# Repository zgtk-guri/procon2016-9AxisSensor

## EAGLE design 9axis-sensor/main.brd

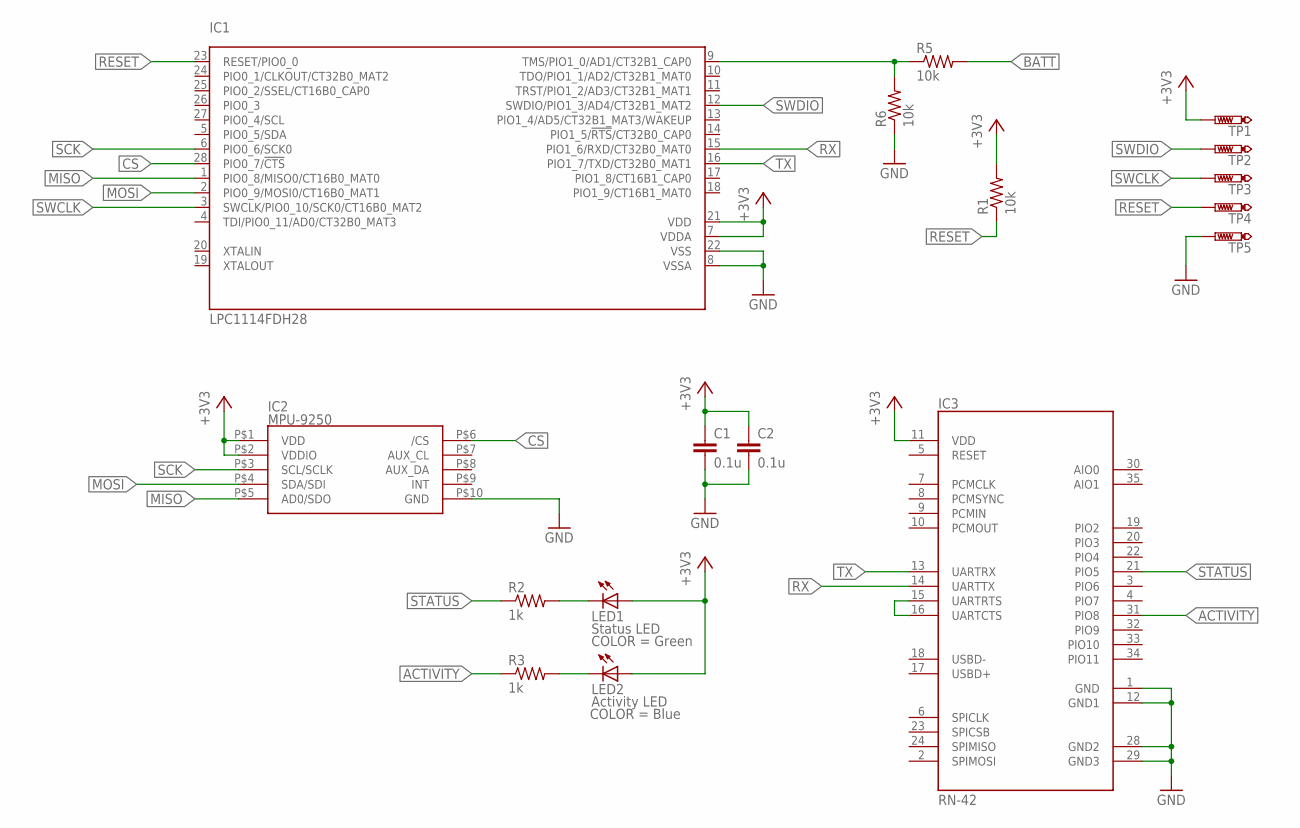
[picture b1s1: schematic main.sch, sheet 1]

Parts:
C1, C2: 0.1u; C0603
IC1: LPC1114FDH28; SOT361-1; MPN LPC1114FDH28/102
IC2: MPU-9250; DIP10S
IC3: RN-42; RN41; MPN RN-42-I/RM
LED1: Status LED; CHIP-LED0603; MPN OSYG1608C1A
LED2: Activity LED; CHIP-LED0603; MPN OSBL1608C1A
R1, R5, R6: 10k; R0603
R2, R3: 1k; R0603
TP1: 3V3; B1,27
TP2: SWDIO; B1,27
TP3: SWCLK; B1,27
TP4: RESET; B1,27
TP5: GND; B1,27

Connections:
+3V3: C1.1, C2.1, IC1.7 (VDDA), IC1.21 (VDD), IC2.P$1 (VDD), IC2.P$2 (VDDIO), IC3.11 (VDD), LED1.A, LED2.A, R1.2, TP1.TP; also elsewhere on the board
ACTIVITY: IC3.31 (PIO8), R3.1
BATT: R5.2; also elsewhere on the board
CS: IC1.28 (PIO0_7/!CTS!), IC2.P$6 (/CS)
GND: C1.2, C2.2, IC1.8 (VSSA), IC1.22 (VSS), IC2.P$10 (GND), IC3.1 (GND), IC3.12 (GND1), IC3.28 (GND2), IC3.29 (GND3), R6.1, TP5.TP; also elsewhere on the board
MISO: IC1.1 (PIO0_8/MISO0/CT16B0_MAT0), IC2.P$5 (AD0/SDO)
MOSI: IC1.2 (PIO0_9/MOSI0/CT16B0_MAT1), IC2.P$4 (SDA/SDI)
unnamed: IC3.15 (UARTRTS), IC3.16 (UARTCTS)
unnamed: LED1.C, R2.2
unnamed: LED2.C, R3.2
unnamed: IC1.9 (TMS/PIO1_0/AD1/CT32B1_CAP0), R5.1, R6.2
RESET: IC1.23 (RESET/PIO0_0), R1.1, TP4.TP
RX: IC1.15 (PIO1_6/RXD/CT32B0_MAT0), IC3.14 (UARTTX)
SCK: IC1.6 (PIO0_6/SCK0), IC2.P$3 (SCL/SCLK)
STATUS: IC3.21 (PIO5), R2.1
SWCLK: IC1.3 (SWCLK/PIO0_10/SCK0/CT16B0_MAT2), TP3.TP
SWDIO: IC1.12 (SWDIO/PIO1_3/AD4/CT32B1_MAT2), TP2.TP
TX: IC1.16 (PIO1_7/TXD/CT32B0_MAT1), IC3.13 (UARTRX)

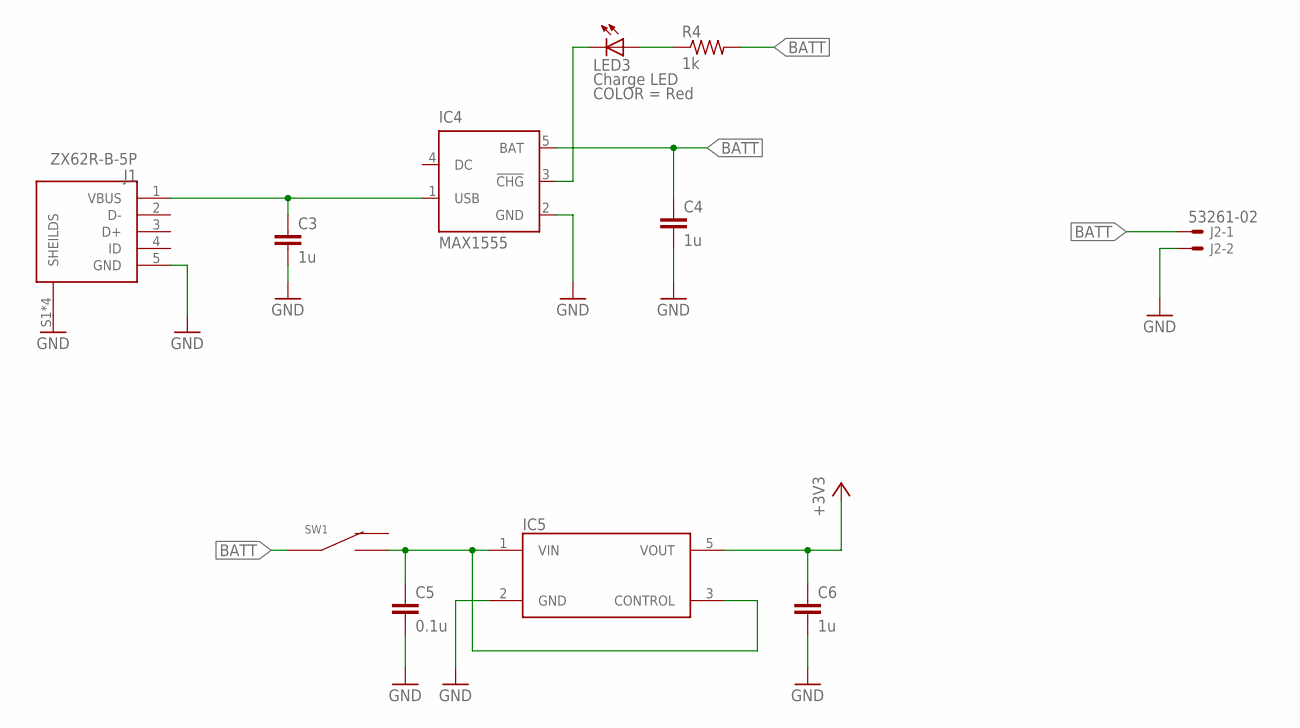
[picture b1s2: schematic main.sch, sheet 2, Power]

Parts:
C3, C4, C6: 1u; C0603
C5: 0.1u; C0603
IC4: MAX1555; SOT23-5L
IC5: NJM2866F33; SOT23-5L
J1: ZX62R-B-5P; MPN ZX62R-B-5P
J2: 53261-02; MPN 53261-0271
LED3: Charge LED; CHIP-LED0603; MPN OSHR1608C1A
R4: 1k; R0603
SW1: SK-12D01-VG4

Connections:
+3V3: C6.1, IC5.5 (VOUT); also elsewhere on the board
BATT: C4.1, IC4.5 (BAT), J2.1, R4.2, SW1.P$2; also elsewhere on the board
GND: C3.2, C4.2, C5.2, C6.2, IC4.2 (GND), IC5.2 (GND), J1.5 (GND), J1.S1 (SHEILDS), J1.S2 (SHEILDS), J1.S3 (SHEILDS), J1.S4 (SHEILDS), J2.2; also elsewhere on the board
unnamed: C3.1, IC4.1 (USB), J1.1 (VBUS)
unnamed: IC4.3 (!CHG), LED3.C
unnamed: LED3.A, R4.1
unnamed: C5.1, IC5.1 (VIN), IC5.3 (CONTROL), SW1.P$3

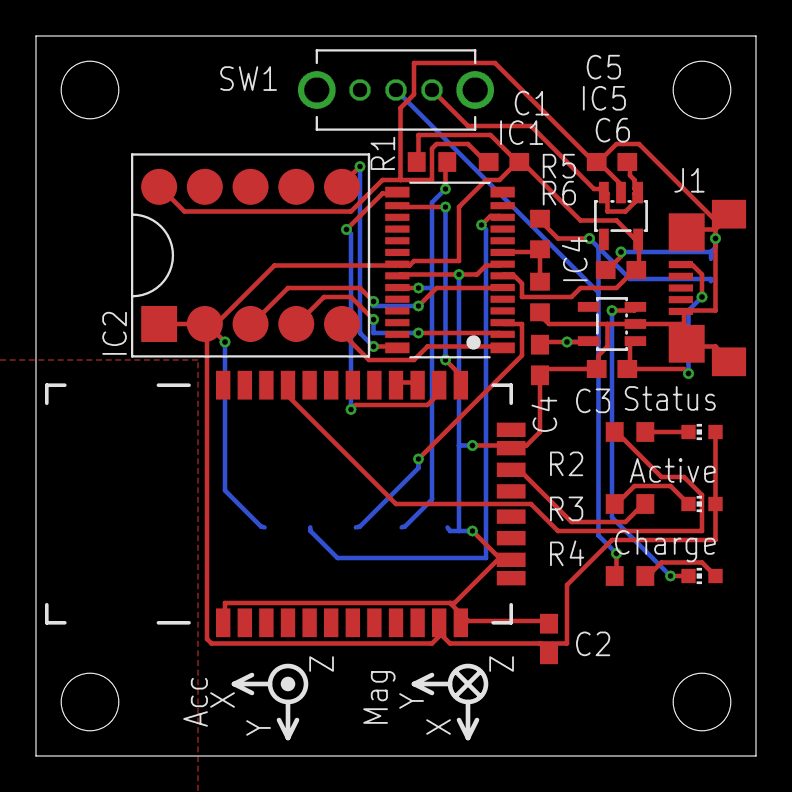
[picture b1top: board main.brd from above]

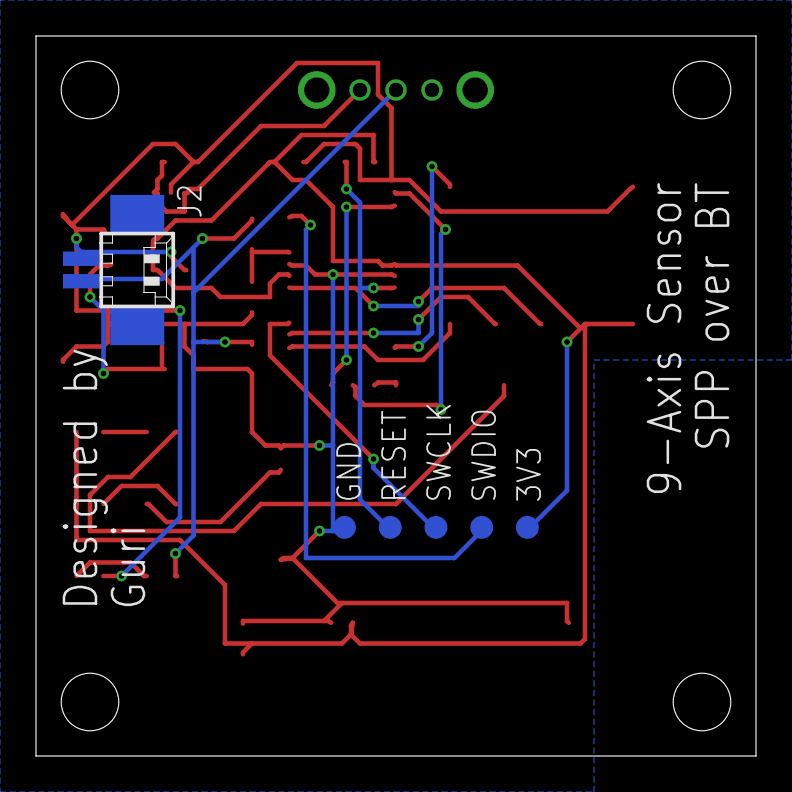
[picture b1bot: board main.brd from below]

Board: 2 copper layers, 40.0 x 40.0 mm, 28 parts (6 on the bottom side), 22 nets.

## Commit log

2016-04-29 プロジェクトを作成
2016-04-30 マイコン、センサを追加
2016-05-09 基板1版できた。
2016-05-11 バッテリ電圧測定回路を追加。基板更新。
2016-05-11 部品番号を記載
2016-05-11 ガーバーを出力
2016-05-17 ADCの配線ミスを修正
2016-05-17 チップ部品サイズを1608に変更

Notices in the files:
parts and their libraries:
SparkFun-RF: Licensing: Creative Commons ShareAlike 4.0 International - https://creativecommons.org/licenses/by-sa/4.0
